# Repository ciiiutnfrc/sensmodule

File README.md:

# Módulo sensor de código abierto para robot móvil

El módulo de sensores consta de dos componentes principales:
1. un anillo de sensores de ultrasonido o sonar (Sonar NAvigation and Ranging) para medición de distancia
1. una unidad de medición inercial, que integra un acelerómetro y un giroscopio (IMU, Inertial Measurement Unit)

Para sujetar y distribuir los transductores de ultrasonido como anillo circular se diseñó un soporte mecánico especı́fico. Todo el conjunto se aloja en un gabinete dedicado fabricado con impresión 3D. El diseño electrónico fue realizado utilizando [KiCAD](https://www.kicad.org/), mientras que para el diseño mecánico del soporte de los transductores y el gabinete se utilizó [FreeCAD](https://www.freecad.org/); ambos decódigo abierto.

Está implementado en base a la placa de desarrollo ["Raspberry Pi Pico"](https://www.raspberrypi.com/documentation/microcontrollers/pico-series.html#pico1), cuyo firmware actúa como nodo de [ROS](https://www.ros.org/) utilizando el framework [micro-ROS](https://micro.vulcanexus.org/). Este nodo es responsable de adquirir los datos de todos los sensores y publicarlos en los topics correspondientes para su procesamiento en la computadora principal del robot.

## Videos
* [ModSens - sensores de distancia por ultrasonido](https://www.youtube.com/watch?v=mX4Z-RGdCro)
* [ModSens - visualización RViz sobre el robot RoMAA-II](https://www.youtube.com/watch?v=sf0R5RFJkfc)
* [ModSens - sensores inerciales](https://www.youtube.com/watch?v=RdyZEUkLeZU)

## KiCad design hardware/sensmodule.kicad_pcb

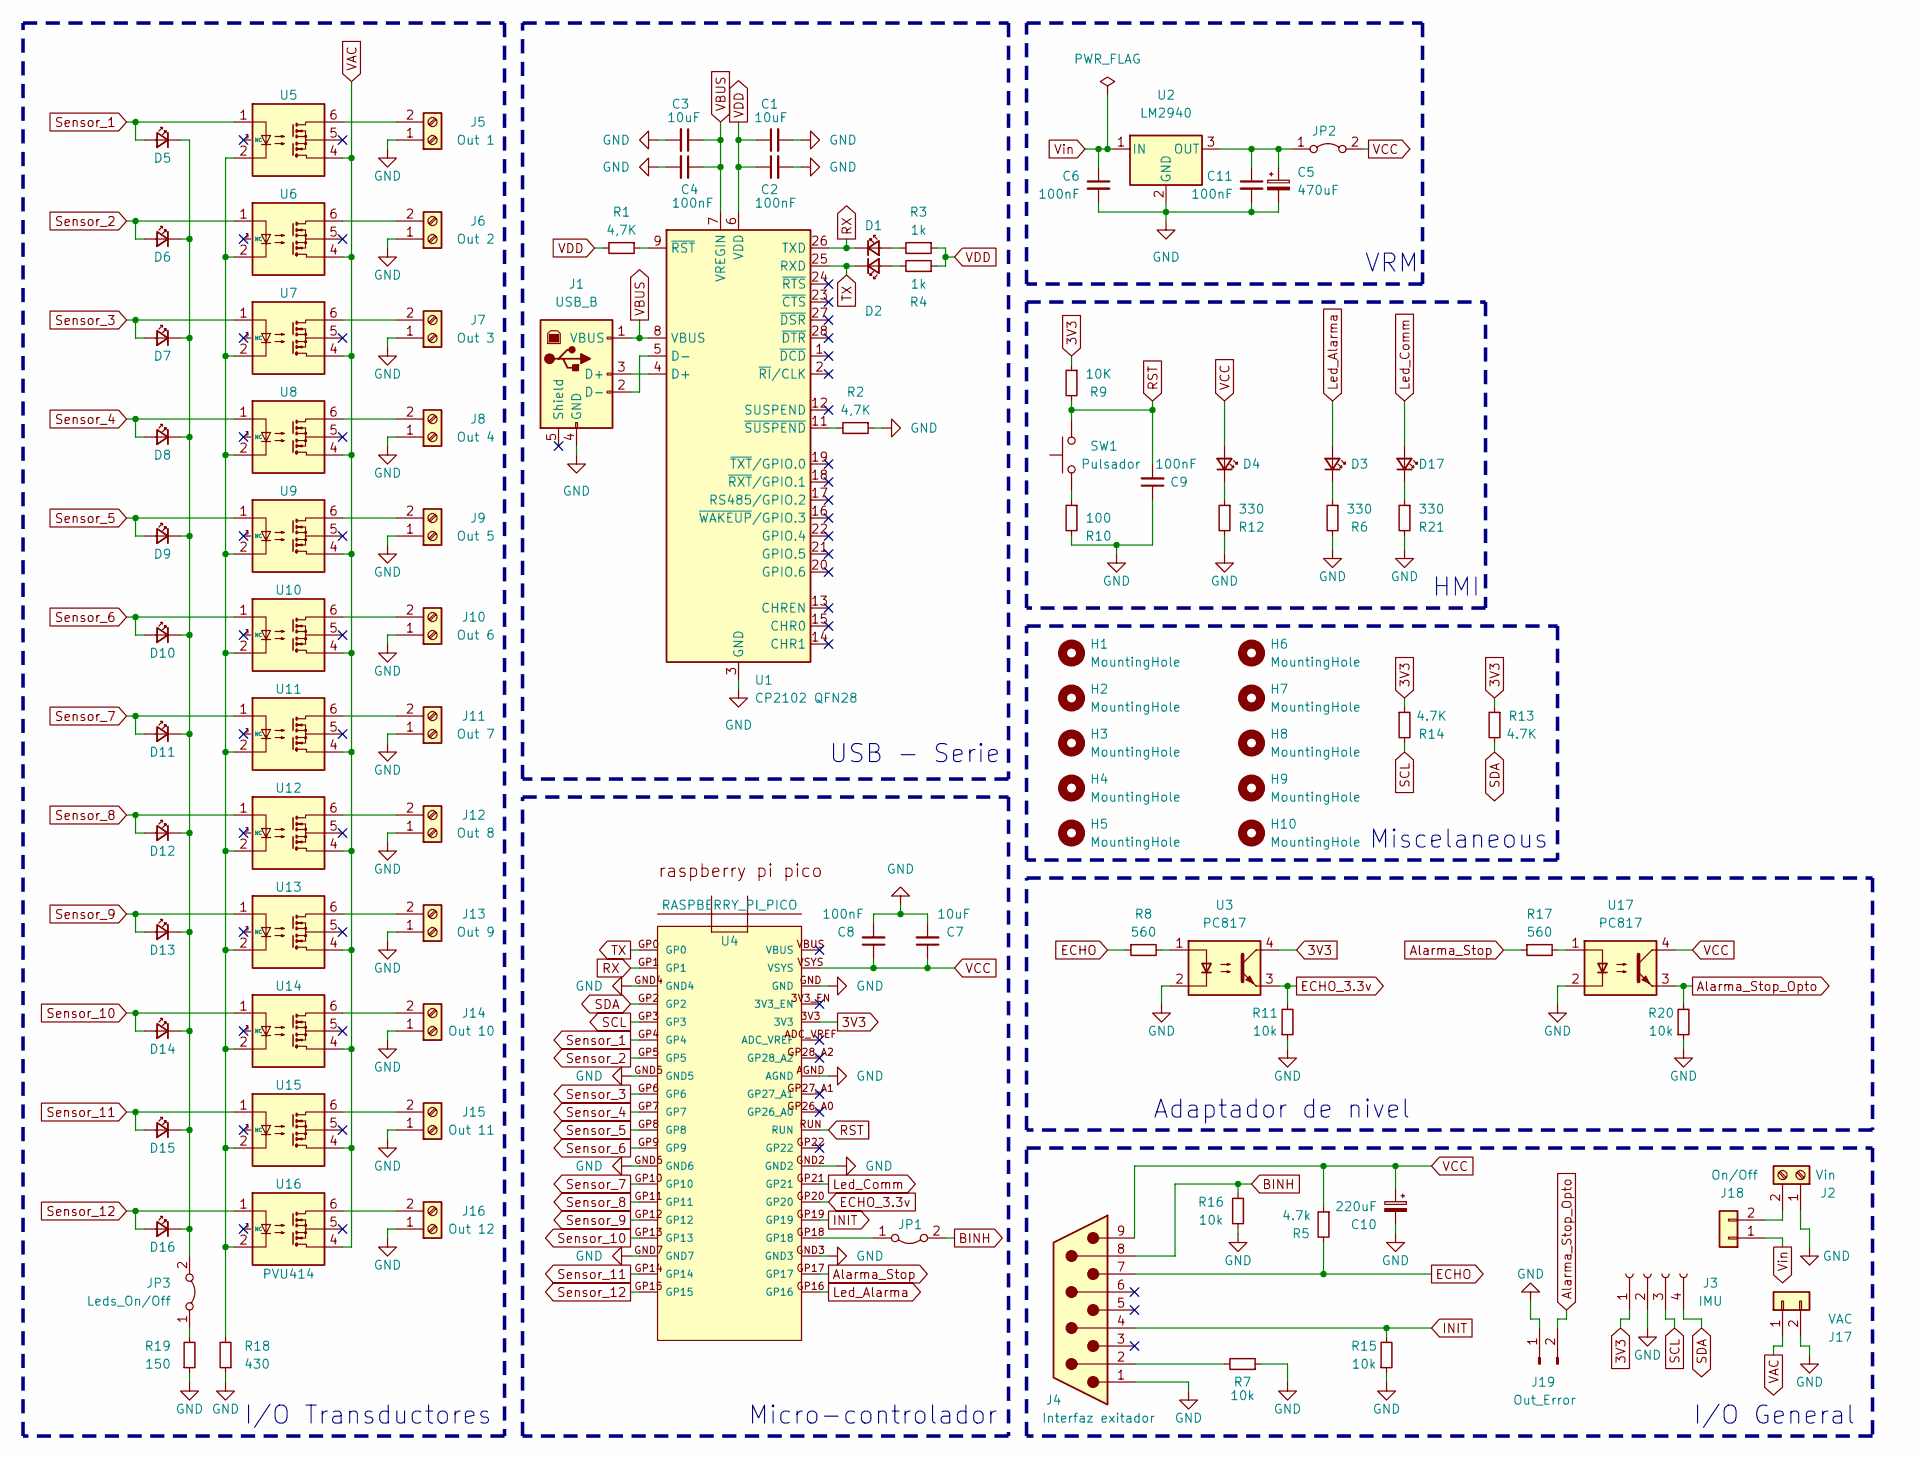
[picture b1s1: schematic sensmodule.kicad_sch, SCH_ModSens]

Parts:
C1, C3, C7: 10uF; C_0805_2012Metric_Pad1.18x1.45mm_HandSolder
C2, C4, C6, C8, C9, C11: 100nF; C_0805_2012Metric_Pad1.18x1.45mm_HandSolder
C5: 470uF; CP_Radial_D6.3mm_P2.50mm
C10: 220uF; CP_Radial_D5.0mm_P2.00mm
D1: TX LED Verde; LED_D3.0mm_Clear
D2: RX LED Azul; LED_D3.0mm_Clear
D3, D17: LED Verde 3mm; PinHeader_1x02_P2.54mm_Vertical
D4: LED Amarillo 3mm; PinHeader_1x02_P2.54mm_Vertical
D5, D6, D7, D8, D9, D10, D11, D12, D13, D14, D15, D16: LED Rojo 3mm; LED_D3.0mm_Clear
H1, H2, H3, H4, H5, H6, H7, H8, H9, H10: MountingHole; MountingHole_3.2mm_M3
J1: USB_B; USB_B_OST_USB-B1HSxx_Horizontal
J2: Vin; PhoenixContact_MC_1,5_2-G-5.08_1x02_P5.08mm_Horizontal
J3: IMU; PinSocket_1x04_P2.54mm_Vertical
J4: Interfaz exitador; Molex_Picoflex_90325-0010_2x05_P1.27mm_Vertical
J5: Out 1; PhoenixContact_MC_1,5_2-G-5.08_1x02_P5.08mm_Horizontal
J6: Out 2; PhoenixContact_MC_1,5_2-G-5.08_1x02_P5.08mm_Horizontal
J7: Out 3; PhoenixContact_MC_1,5_2-G-5.08_1x02_P5.08mm_Horizontal
J8: Out 4; PhoenixContact_MC_1,5_2-G-5.08_1x02_P5.08mm_Horizontal
J9: Out 5; PhoenixContact_MC_1,5_2-G-5.08_1x02_P5.08mm_Horizontal
J10: Out 6; PhoenixContact_MC_1,5_2-G-5.08_1x02_P5.08mm_Horizontal
J11: Out 7; PhoenixContact_MC_1,5_2-G-5.08_1x02_P5.08mm_Horizontal
J12: Out 8; PhoenixContact_MC_1,5_2-G-5.08_1x02_P5.08mm_Horizontal
J13: Out 9; PhoenixContact_MC_1,5_2-G-5.08_1x02_P5.08mm_Horizontal
J14: Out 10; PhoenixContact_MC_1,5_2-G-5.08_1x02_P5.08mm_Horizontal
J15: Out 11; PhoenixContact_MC_1,5_2-G-5.08_1x02_P5.08mm_Horizontal
J16: Out 12; PhoenixContact_MC_1,5_2-G-5.08_1x02_P5.08mm_Horizontal
J17: VAC; Molex_KK-254_AE-6410-02A_1x02_P2.54mm_Vertical
J18: On/Off; Molex_KK-254_AE-6410-02A_1x02_P2.54mm_Vertical
J19: Out_Error; PinHeader_1x02_P2.54mm_Vertical
JP1: BINH_On/Off; SolderJumper-2_P1.3mm_Open_Pad1.0x1.5mm
JP2: Main_On/Off; SolderJumper-2_P1.3mm_Open_Pad1.0x1.5mm
JP3: Leds_On/Off; PinHeader_1x02_P2.54mm_Vertical
R1, R2: 4,7K; R_0805_2012Metric_Pad1.20x1.40mm_HandSolder
R3, R4: 1k; R_0805_2012Metric_Pad1.20x1.40mm_HandSolder
R5: 4.7k; R_0805_2012Metric_Pad1.20x1.40mm_HandSolder
R6, R12, R21: 330; R_0805_2012Metric_Pad1.20x1.40mm_HandSolder
R7, R11, R15, R16, R20: 10k; R_0805_2012Metric_Pad1.20x1.40mm_HandSolder
R8, R17: 560; R_0805_2012Metric_Pad1.20x1.40mm_HandSolder
R9: 10K; R_0805_2012Metric_Pad1.20x1.40mm_HandSolder
R10: 100; R_0805_2012Metric_Pad1.20x1.40mm_HandSolder
R13, R14: 4.7K; R_0805_2012Metric_Pad1.20x1.40mm_HandSolder
R18: 430; R_0805_2012Metric_Pad1.20x1.40mm_HandSolder
R19: 150; R_0805_2012Metric_Pad1.20x1.40mm_HandSolder
SW1: Pulsador; SW_SPST_Omron_B3F-315x_Angled
U1: CP2102 QFN28; QFN-28-1EP_5x5mm_P0.5mm_EP3.35x3.35mm
U2: LM2940; TO-220-3_Horizontal_TabDown
U3, U17: PC817; DIP-4_W7.62mm_Socket_LongPads
U4: RASPBERRY_PI_PICO
U5, U6, U7, U8, U9, U10, U11, U12, U13, U14, U15, U16: PVU414; DIP-6_W7.62mm_Socket_LongPads

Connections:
3V3: J3.1, R9.1, R13.1, R14.1, U3.4, U4.3V3
Alarma_Stop: R17.1, U4.GP17
Alarma_Stop_Opto: J19.2, R20.2, U17.3
BINH: J4.8, JP1.2 (B), R16.2
ECHO: J4.7, R5.2, R8.1
ECHO_3.3v: R11.2, U3.3, U4.GP20
GND: C1.2, C2.2, C3.2, C4.2, C5.2, C6.2, C7.2, C8.2, C9.1, C10.2, C11.2, J1.4 (GND), J2.1, J3.2, J4.1, J5.1, J6.1, J7.1, J8.1, J9.1, J10.1, J11.1, J12.1, J13.1, J14.1, J15.1, J16.1, J17.2, J19.1, R2.1, R6.2, R7.1, R10.2, R11.1, R12.2, R15.1, R16.1, R18.1, R19.1, R20.1, R21.2, U1.3 (GND), U1.29 (GND), U2.2 (GND), U3.2, U4.AGND, U4.GND, U4.GND2, U4.GND3, U4.GND4, U4.GND5, U4.GND6, U4.GND7, U17.2
INIT: J4.4, R15.2, U4.GP19
Led_Alarma: D3.2 (A), U4.GP16
Led_Comm: D17.2 (A), U4.GP21
unnamed: D1.2 (A), R3.2
unnamed: D2.2 (A), R4.2
unnamed: D3.1 (K), R6.1
unnamed: D4.1 (K), R12.1
unnamed: D5.1 (K), D6.1 (K), D7.1 (K), D8.1 (K), D9.1 (K), D10.1 (K), D11.1 (K), D12.1 (K), D13.1 (K), D14.1 (K), D15.1 (K), D16.1 (K), JP3.2 (B)
unnamed: D17.1 (K), R21.1
unnamed: J1.3 (D+), U1.4 (D+)
unnamed: J1.2 (D-), U1.5 (D-)
unnamed: J4.2, R7.2
unnamed: J5.2, U5.6
unnamed: J6.2, U6.6
unnamed: J7.2, U7.6
unnamed: J8.2, U8.6
unnamed: J9.2, U9.6
unnamed: J10.2, U10.6
unnamed: J11.2, U11.6
unnamed: J12.2, U12.6
unnamed: J13.2, U13.6
unnamed: J14.2, U14.6
unnamed: J15.2, U15.6
unnamed: J16.2, U16.6
unnamed: J2.2, J18.2
unnamed: JP1.1 (A), U4.GP18
unnamed: C5.1, C11.1, JP2.1 (A), U2.3 (OUT)
unnamed: JP3.1 (A), R19.2
unnamed: R8.2, U3.1
unnamed: R10.1, SW1.1
unnamed: R17.2, U17.1
unnamed: R18.2, U5.2, U6.2, U7.2, U8.2, U9.2, U10.2, U11.2, U12.2, U13.2, U14.2, U15.2, U16.2
unnamed: R1.1, U1.9 (~RST)
unnamed: R2.2, U1.11 (~SUSPEND)
RST: C9.2, R9.2, SW1.2, U4.RUN
RX: D1.1 (K), U1.26 (TXD), U4.GP1
SCL: J3.3, R14.2, U4.GP3
SDA: J3.4, R13.2, U4.GP2
Sensor_1: D5.2 (A), U4.GP4, U5.1
Sensor_2: D6.2 (A), U4.GP5, U6.1
Sensor_3: D7.2 (A), U4.GP6, U7.1
Sensor_4: D8.2 (A), U4.GP7, U8.1
Sensor_5: D9.2 (A), U4.GP8, U9.1
Sensor_6: D10.2 (A), U4.GP9, U10.1
Sensor_7: D11.2 (A), U4.GP10, U11.1
Sensor_8: D12.2 (A), U4.GP11, U12.1
Sensor_9: D13.2 (A), U4.GP12, U13.1
Sensor_10: D14.2 (A), U4.GP13, U14.1
Sensor_11: D15.2 (A), U4.GP14, U15.1
Sensor_12: D16.2 (A), U4.GP15, U16.1
TX: D2.1 (K), U1.25 (RXD), U4.GP0
VAC: J17.1, U5.4, U6.4, U7.4, U8.4, U9.4, U10.4, U11.4, U12.4, U13.4, U14.4, U15.4, U16.4
VBUS: C3.1, C4.1, J1.1 (VBUS), U1.7 (VREGIN), U1.8 (VBUS)
VCC: C7.1, C8.1, C10.1, D4.2 (A), J4.9, JP2.2 (B), R5.1, U4.VSYS, U17.4
VDD: C1.1, C2.1, R1.2, R3.1, R4.1, U1.6 (VDD)
Vin: C6.1, J18.1, U2.1 (IN)

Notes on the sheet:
Adaptador de nivel
VRM
Micro-controlador
I/O General
Miscelaneous
I/O Transductores
USB - Serie
HMI

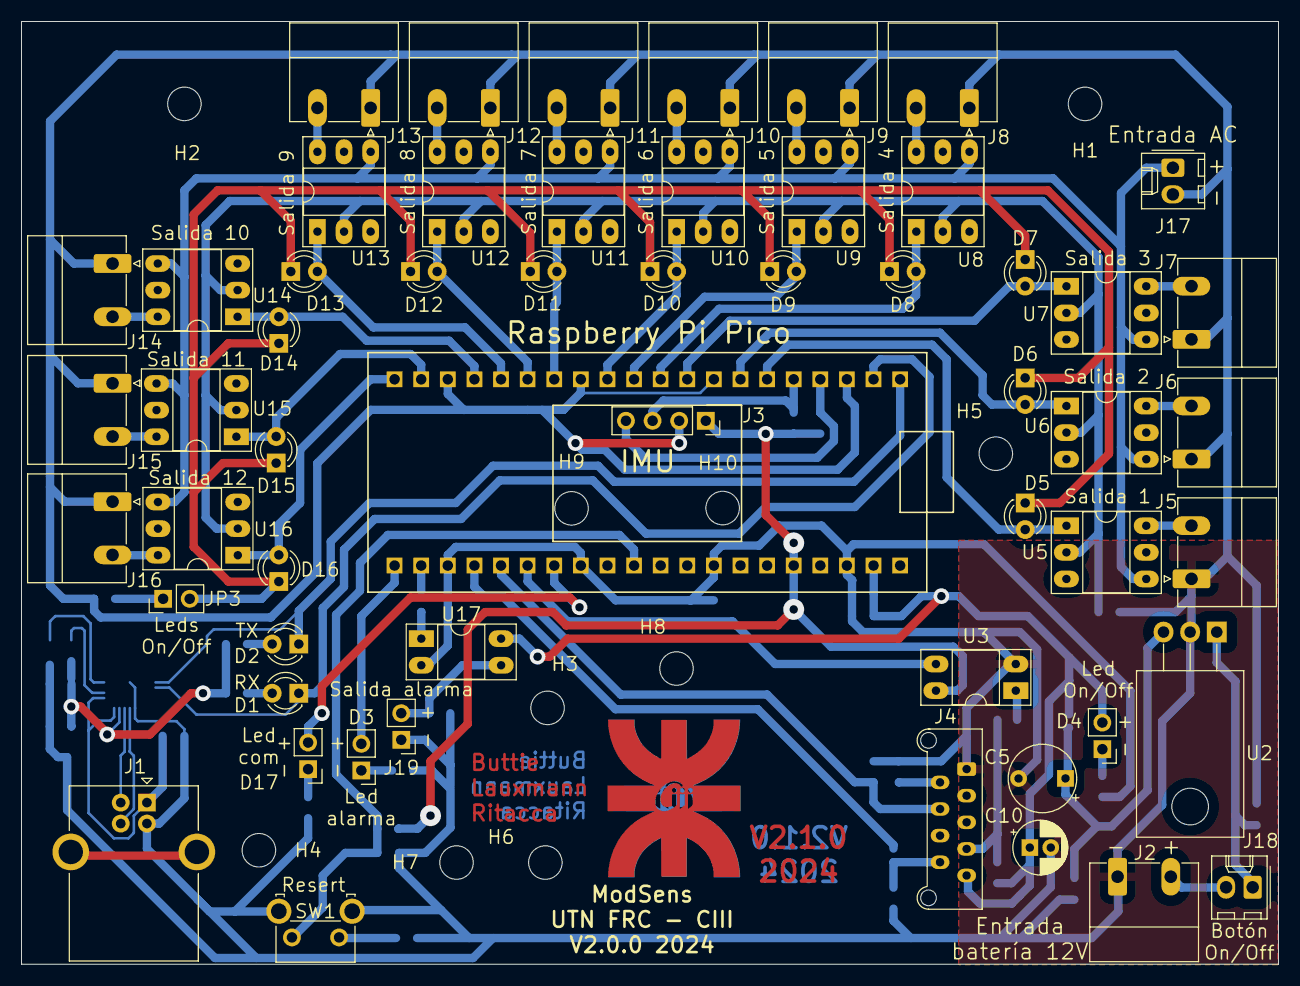
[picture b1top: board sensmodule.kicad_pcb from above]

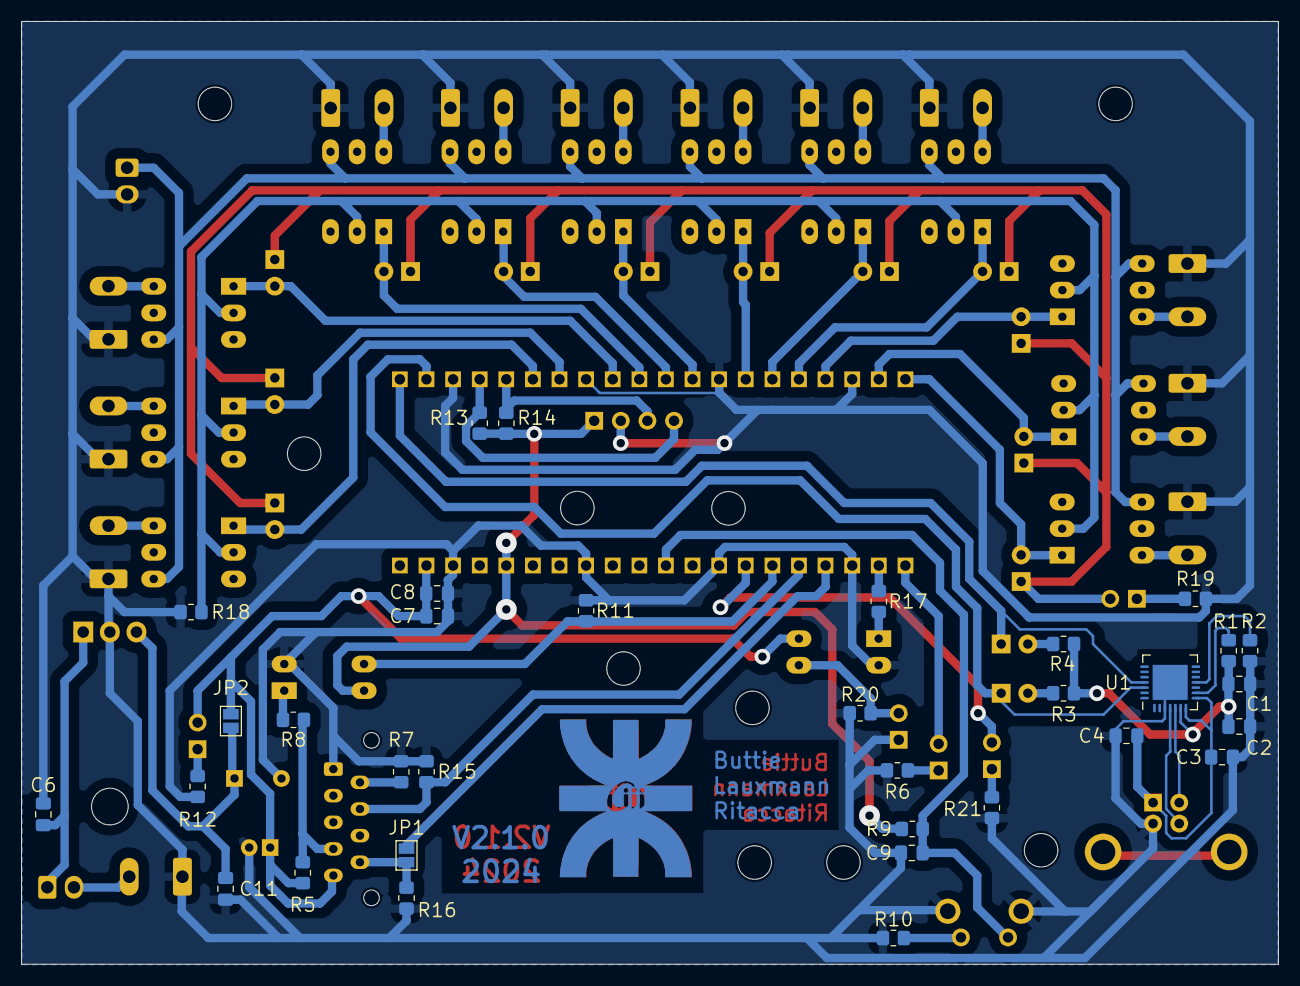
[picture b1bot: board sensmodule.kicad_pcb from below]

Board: 2 copper layers, 120.0 x 90.0 mm, 99 parts (33 on the bottom side), 63 nets.

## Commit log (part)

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2026-01-29 Add KiCAD files of the sensor module board
2026-02-03 Add missing 3D models :pencil:
2026-06-01 Add source files for micro-ROS node
